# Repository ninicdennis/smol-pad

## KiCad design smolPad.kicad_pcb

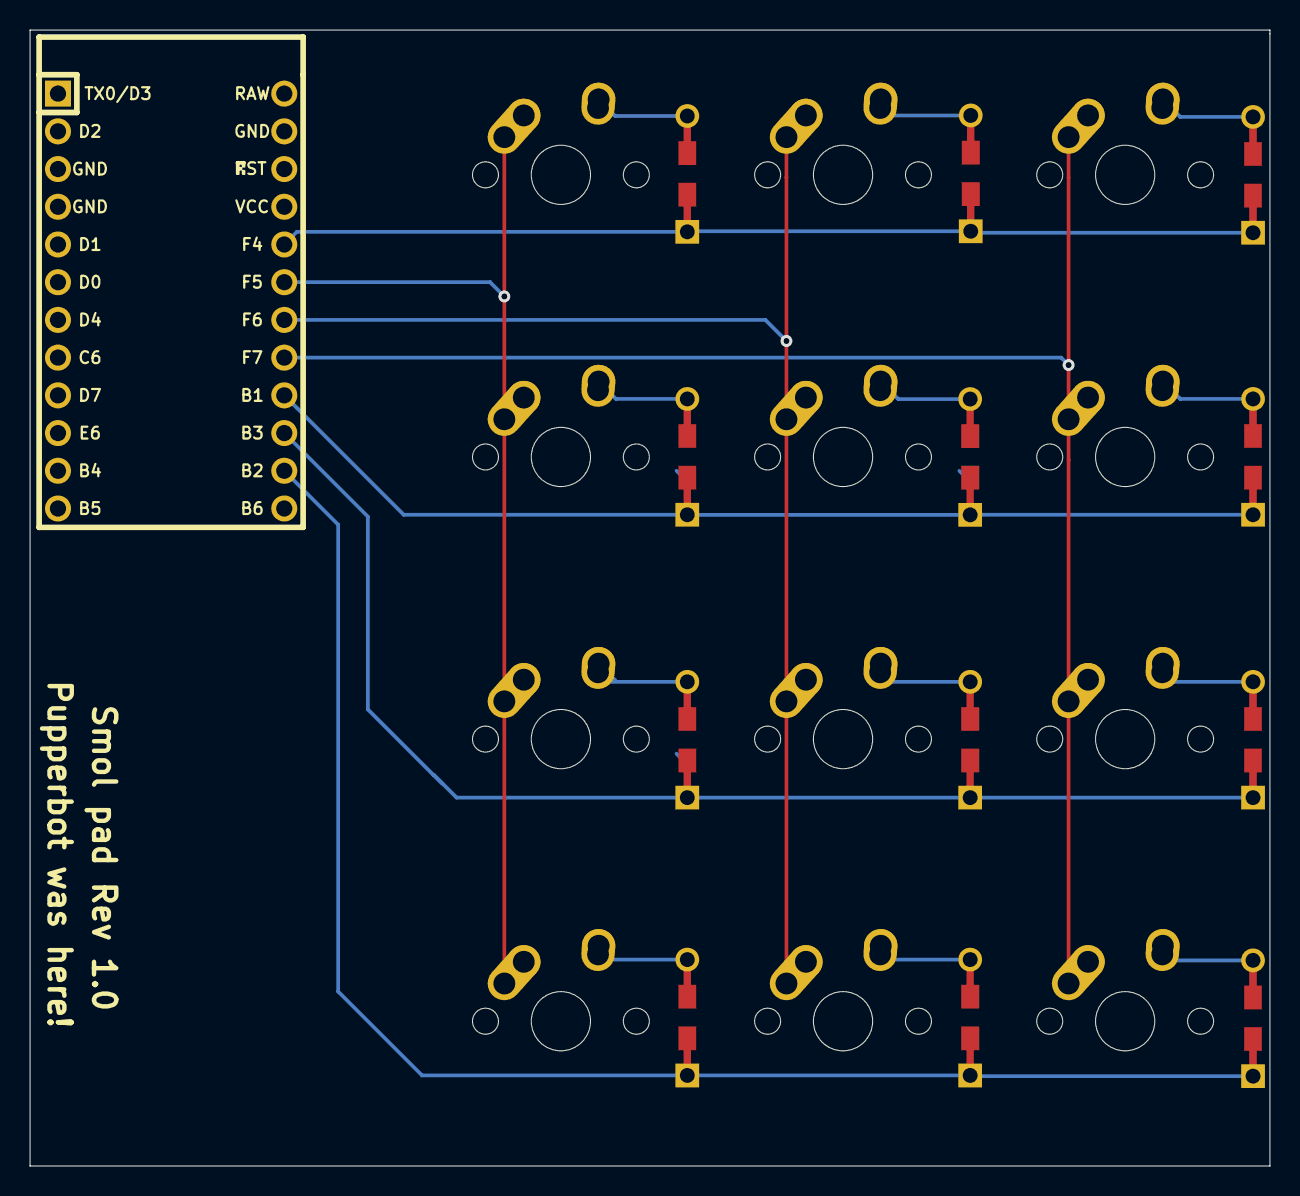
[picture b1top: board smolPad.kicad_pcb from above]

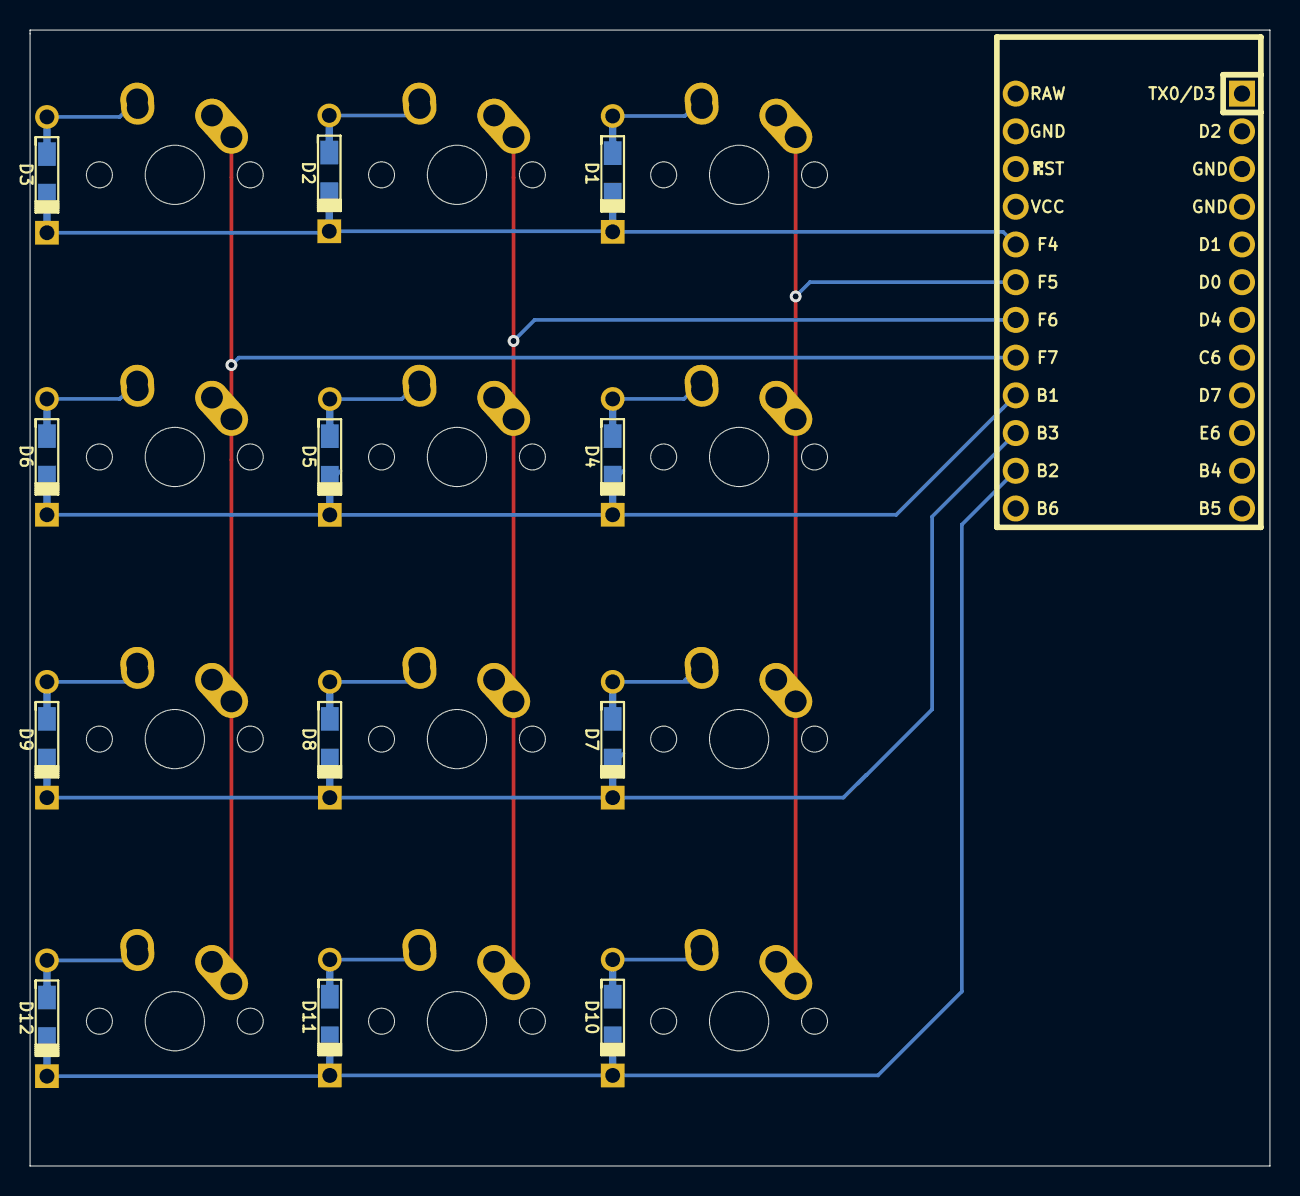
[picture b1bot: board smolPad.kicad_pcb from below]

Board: 2 copper layers, 83.5 x 76.5 mm, 25 parts (12 on the bottom side), 19 nets.

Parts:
D1, D2, D3, D4, D5, D6, D7, D8, D9, D10, D11, D12: D_Small; Diode-dual
MX1, MX2, MX3, MX4, MX5, MX6, MX7, MX8, MX9, MX10, MX11, MX12: MX-NoLED; MX-1U-NoLED
U1: ProMicro; ArduinoProMicro

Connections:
COL0: MX1.1, MX4.1, MX7.1, MX10.1, U1.19
COL1: MX2.1, MX5.1, MX8.1, MX11.1, U1.18
COL2: MX3.1, MX6.1, MX9.1, MX12.1, U1.17
unnamed: D1.2, MX1.2
unnamed: D2.2, MX2.2
unnamed: D3.2, MX3.2
unnamed: D4.2, MX4.2
unnamed: D5.2, MX5.2
unnamed: D6.2, MX6.2
unnamed: D7.2, MX7.2
unnamed: D8.2, MX8.2
unnamed: D9.2, MX9.2
unnamed: D10.2, MX10.2
unnamed: D11.2, MX11.2
unnamed: D12.2, MX12.2
ROW0: D1.1, D2.1, D3.1, U1.20
ROW1: D4.1, D5.1, D6.1, U1.16
ROW2: D7.1, D8.1, D9.1, U1.15
ROW3: D10.1, D11.1, D12.1, U1.14

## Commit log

2020-08-23 Updated design to use both THT and SMD Diodes. Silkscreen added as well.
2020-08-23 Added gerbers.
